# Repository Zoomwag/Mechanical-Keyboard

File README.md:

# Mechanical Keyboard

These are some high-quality renders of the keyboard design.

---

## Overview

This is a custom mechanical keyboard that I designed from scratch. It is a **60% layout** and runs on a **Raspberry Pi Pico** using **QMK firmware**.

The goal of this project was to make the keyboard:
- Easy to build  
- Affordable and accessible  
- Fully DIY-friendly  

All components are **through-hole (THT)**, making soldering much easier—especially for beginners. The entire keyboard is assembled using just **four M3 screws**, keeping the construction simple and clean.

The case is fully **3D printable**, and the keycaps can either be 3D printed or purchased. I recommend buying keycaps for better durability and finish.

The keyboard uses **Cherry MX-style switches**, so you can choose whichever type suits your preference. I will likely be using **Cherry MX Red switches** for a smooth, linear feel.

---

## PCB

### PCB Layout

### Schematic

### 3D PCB Model

### Fully Assembled PCB (3D View)

---

## Case

### Top Shell

### Bottom Shell

### Full Case (No Electronics)

### Electronics Installed

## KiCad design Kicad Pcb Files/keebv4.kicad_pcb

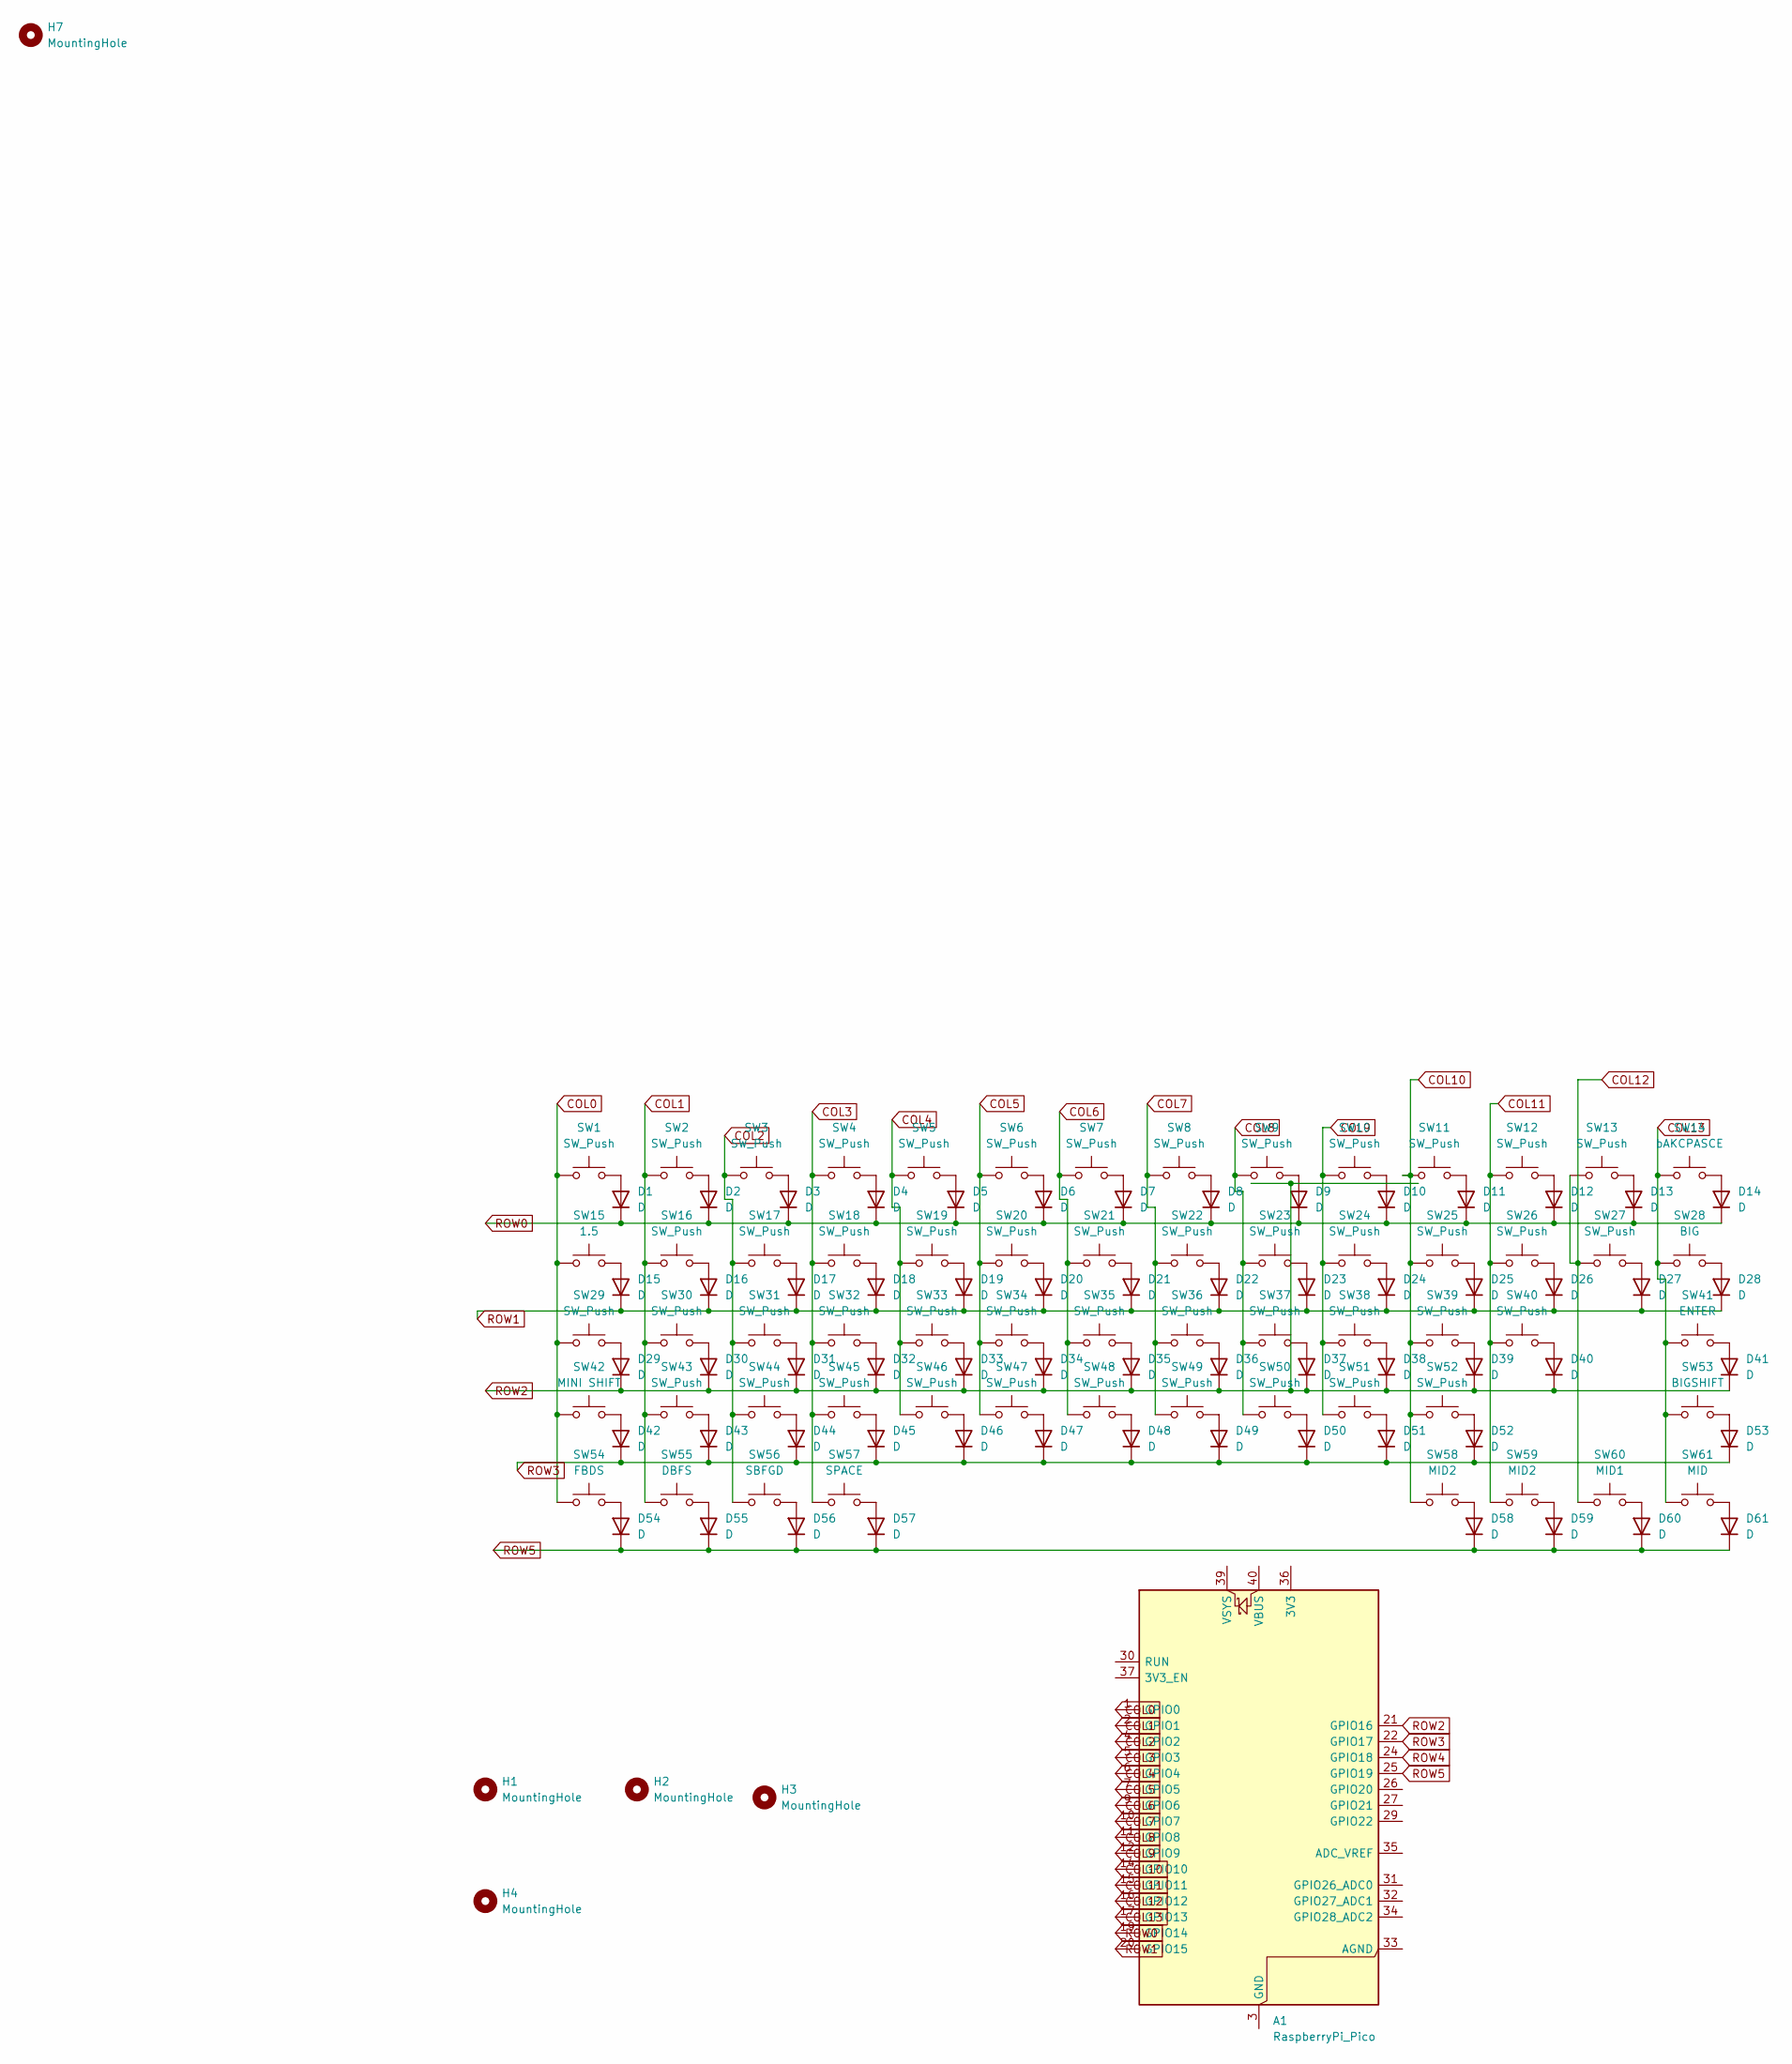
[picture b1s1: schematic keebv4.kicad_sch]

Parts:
A1: RaspberryPi_Pico; RaspberryPi_Pico_Common_Unspecified
D1, D2, D3, D4, D5, D6, D7, D8, D9, D10, D11, D12, D13, D14, D15, D16, D17, D18, D19, D20, D21, D22, D23, D24, D25, D26, D27, D28, D29, D30, D31, D32, D33, D34, D35, D36, D37, D38, D39, D40, D41, D42, D43, D44, D45, D46, D47, D48, D49, D50, D51, D52, D53, D54, D55, D56, D57, D58, D59, D60, D61: D; D_DO-35_SOD27_P7.62mm_Horizontal
H1, H2, H3, H4, H7: MountingHole; MountingHole_3.2mm_M3
SW1, SW2, SW3, SW4, SW5, SW6, SW7, SW8, SW9, SW10, SW11, SW12, SW13, SW16, SW17, SW18, SW19, SW20, SW21, SW22, SW23, SW24, SW25, SW26, SW27, SW30, SW31, SW32, SW33, SW34, SW35, SW36, SW37, SW38, SW39, SW40, SW43, SW44, SW45, SW46, SW47, SW48, SW49, SW50, SW51, SW52: SW_Push; SW_Cherry_MX_1.00u_PCB
SW14: bAKCPASCE; SW_Cherry_MX_2.00u_PCB
SW15: 1.5; SW_Cherry_MX_1.00u_PCB
SW28: BIG; SW_Cherry_MX_1.50u_PCB
SW29: SW_Push; SW_Cherry_MX_1.75u_PCB
SW41: ENTER; SW_Cherry_MX_2.25u_PCB
SW42: MINI SHIFT; SW_Cherry_MX_2.25u_PCB
SW53: BIGSHIFT; SW_Cherry_MX_2.75u_PCB
SW54: FBDS; SW_Cherry_MX_1.25u_PCB
SW55: DBFS; SW_Cherry_MX_1.25u_PCB
SW56: SBFGD; SW_Cherry_MX_1.25u_PCB
SW57: SPACE; SW_Cherry_MX_6.25u_PCB
SW58, SW59: MID2; SW_Cherry_MX_1.25u_PCB
SW60: MID1; SW_Cherry_MX_1.25u_PCB
SW61: MID; SW_Cherry_MX_1.25u_PCB

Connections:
COL0: A1.1 (GPIO0), SW1.1, SW15.1, SW29.1, SW42.1, SW54.1
COL1: A1.2 (GPIO1), SW2.1, SW16.1, SW30.1, SW43.1, SW55.1
COL2: A1.4 (GPIO2), SW3.1, SW17.1, SW31.1, SW44.1, SW56.1
COL3: A1.5 (GPIO3), SW4.1, SW18.1, SW32.1, SW45.1, SW57.1
COL4: A1.6 (GPIO4), SW5.1, SW19.1, SW33.1, SW46.1
COL5: A1.7 (GPIO5), SW6.1, SW20.1, SW34.1, SW47.1
COL6: A1.9 (GPIO6), SW7.1, SW21.1, SW35.1, SW48.1
COL7: A1.10 (GPIO7), SW8.1, SW22.1, SW36.1, SW49.1
COL8: A1.11 (GPIO8), SW9.1, SW23.1, SW37.1, SW50.1
COL9: A1.12 (GPIO9), SW10.1, SW24.1, SW38.1, SW51.1
COL10: A1.14 (GPIO10), SW11.1, SW25.1, SW39.1, SW52.1, SW58.1
COL11: A1.15 (GPIO11), SW12.1, SW26.1, SW40.1, SW59.1
COL12: A1.16 (GPIO12), SW13.1, SW27.1, SW60.1
COL13: A1.17 (GPIO13), SW14.1, SW28.1, SW41.1, SW53.1, SW61.1
unnamed: A1.3 (GND), A1.8 (GND), A1.13 (GND), A1.18 (GND), A1.23 (GND), A1.28 (GND), A1.38 (GND)
unnamed: D1.2 (A), SW1.2
unnamed: D2.2 (A), SW2.2
unnamed: D3.2 (A), SW3.2
unnamed: D4.2 (A), SW4.2
unnamed: D5.2 (A), SW5.2
unnamed: D6.2 (A), SW6.2
unnamed: D7.2 (A), SW7.2
unnamed: D8.2 (A), SW8.2
unnamed: D9.2 (A), SW9.2
unnamed: D10.2 (A), SW10.2
unnamed: D11.2 (A), SW11.2
unnamed: D12.2 (A), SW12.2
unnamed: D13.2 (A), SW13.2
unnamed: D14.2 (A), SW14.2
unnamed: D15.2 (A), SW15.2
unnamed: D16.2 (A), SW16.2
unnamed: D17.2 (A), SW17.2
unnamed: D18.2 (A), SW18.2
unnamed: D19.2 (A), SW19.2
unnamed: D20.2 (A), SW20.2
unnamed: D21.2 (A), SW21.2
unnamed: D22.2 (A), SW22.2
unnamed: D23.2 (A), SW23.2
unnamed: D24.2 (A), SW24.2
unnamed: D25.2 (A), SW25.2
unnamed: D26.2 (A), SW26.2
unnamed: D27.2 (A), SW27.2
unnamed: D28.2 (A), SW28.2
unnamed: D29.2 (A), SW29.2
unnamed: D30.2 (A), SW30.2
unnamed: D31.2 (A), SW31.2
unnamed: D32.2 (A), SW32.2
unnamed: D33.2 (A), SW33.2
unnamed: D34.2 (A), SW34.2
unnamed: D35.2 (A), SW35.2
unnamed: D36.2 (A), SW36.2
unnamed: D37.2 (A), SW37.2
unnamed: D38.2 (A), SW38.2
unnamed: D39.2 (A), SW39.2
unnamed: D40.2 (A), SW40.2
unnamed: D41.2 (A), SW41.2
unnamed: D42.2 (A), SW42.2
unnamed: D43.2 (A), SW43.2
unnamed: D44.2 (A), SW44.2
unnamed: D45.2 (A), SW45.2
unnamed: D46.2 (A), SW46.2
unnamed: D47.2 (A), SW47.2
unnamed: D48.2 (A), SW48.2
unnamed: D49.2 (A), SW49.2
unnamed: D50.2 (A), SW50.2
unnamed: D51.2 (A), SW51.2
unnamed: D52.2 (A), SW52.2
unnamed: D53.2 (A), SW53.2
unnamed: D54.2 (A), SW54.2
unnamed: D55.2 (A), SW55.2
unnamed: D56.2 (A), SW56.2
unnamed: D57.2 (A), SW57.2
unnamed: D58.2 (A), SW58.2
unnamed: D59.2 (A), SW59.2
unnamed: D60.2 (A), SW60.2
unnamed: D61.2 (A), SW61.2
ROW0: A1.19 (GPIO14), D1.1 (K), D2.1 (K), D3.1 (K), D4.1 (K), D5.1 (K), D6.1 (K), D7.1 (K), D8.1 (K), D9.1 (K), D10.1 (K), D11.1 (K), D12.1 (K), D13.1 (K), D14.1 (K)
ROW1: A1.20 (GPIO15), D15.1 (K), D16.1 (K), D17.1 (K), D18.1 (K), D19.1 (K), D20.1 (K), D21.1 (K), D22.1 (K), D23.1 (K), D24.1 (K), D25.1 (K), D26.1 (K), D27.1 (K), D28.1 (K)
ROW2: A1.21 (GPIO16), D29.1 (K), D30.1 (K), D31.1 (K), D32.1 (K), D33.1 (K), D34.1 (K), D35.1 (K), D36.1 (K), D37.1 (K), D38.1 (K), D39.1 (K), D40.1 (K), D41.1 (K)
ROW3: A1.22 (GPIO17), D42.1 (K), D43.1 (K), D44.1 (K), D45.1 (K), D46.1 (K), D47.1 (K), D48.1 (K), D49.1 (K), D50.1 (K), D51.1 (K), D52.1 (K), D53.1 (K)
ROW4: A1.24 (GPIO18)
ROW5: A1.25 (GPIO19), D54.1 (K), D55.1 (K), D56.1 (K), D57.1 (K), D58.1 (K), D59.1 (K), D60.1 (K), D61.1 (K)

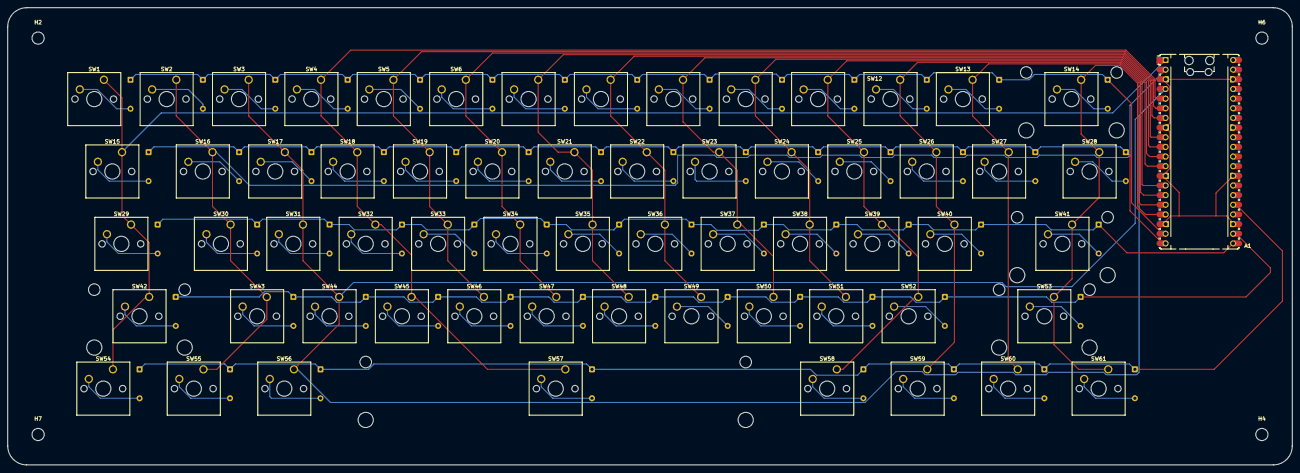
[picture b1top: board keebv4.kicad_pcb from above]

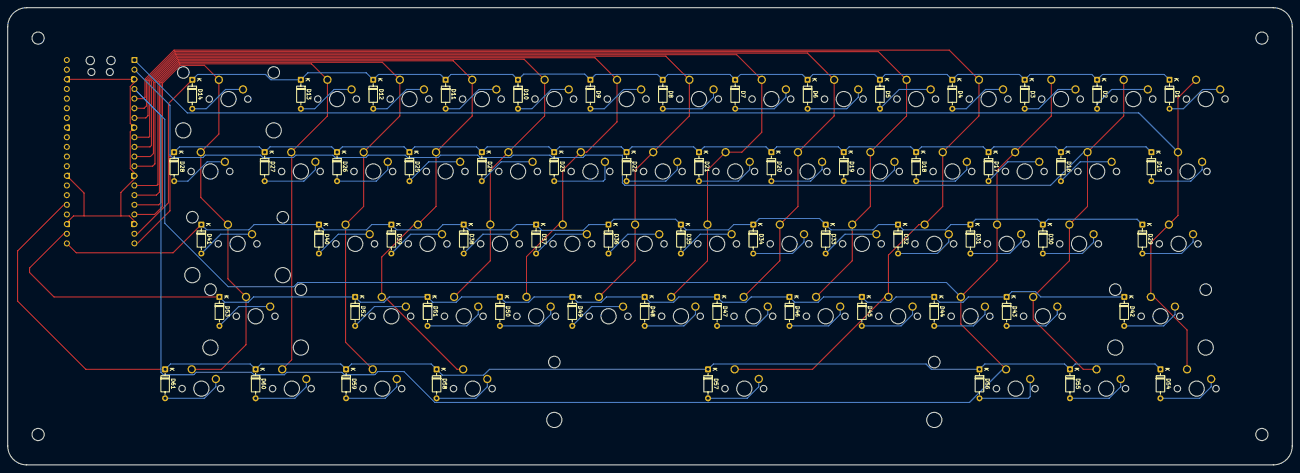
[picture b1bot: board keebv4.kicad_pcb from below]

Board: 2 copper layers, 338.1 x 120.3 mm, 127 parts (61 on the bottom side), 81 nets.

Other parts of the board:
H6: MountingHole; MountingHole_3.2mm_M3

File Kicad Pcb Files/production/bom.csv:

Designator,Footprint,Quantity,Value,LCSC Part #
A1,RaspberryPi_Pico_Common_Unspecified,1,RaspberryPi_Pico,
"D1, D10, D11, D12, D13, D14, D15, D16, D17, D18, D19, D2, D20, D21, D22, D23, D24, D25, D26, D27, D28, D29, D3, D30, D31, D32, D33, D34, D35, D36, D37, D38, D39, D4, D40, D41, D42, D43, D44, D45, D46, D47, D48, D49, D5, D50, D51, D52, D53, D54, D55, D56, D57, D58, D59, D6, D60, D61, D7, D8, D9",D_DO-35_SOD27_P7.62mm_Horizontal,61,D,
"SW1, SW10, SW11, SW12, SW13, SW16, SW17, SW18, SW19, SW2, SW20, SW21, SW22, SW23, SW24, SW25, SW26, SW27, SW3, SW30, SW31, SW32, SW33, SW34, SW35, SW36, SW37, SW38, SW39, SW4, SW40, SW43, SW44, SW45, SW46, SW47, SW48, SW49, SW5, SW50, SW51, SW52, SW6, SW7, SW8, SW9",SW_Cherry_MX_1.00u_PCB,46,SW_Push,
SW14,SW_Cherry_MX_2.00u_PCB,1,bAKCPASCE,
SW15,SW_Cherry_MX_1.00u_PCB,1,1.5,
SW28,SW_Cherry_MX_1.50u_PCB,1,BIG,
SW29,SW_Cherry_MX_1.75u_PCB,1,SW_Push,
SW41,SW_Cherry_MX_2.25u_PCB,1,ENTER,
SW42,SW_Cherry_MX_2.25u_PCB,1,MINI SHIFT,
SW53,SW_Cherry_MX_2.75u_PCB,1,BIGSHIFT,
SW54,SW_Cherry_MX_1.25u_PCB,1,FBDS,
SW55,SW_Cherry_MX_1.25u_PCB,1,DBFS,
SW56,SW_Cherry_MX_1.25u_PCB,1,SBFGD,
SW57,SW_Cherry_MX_6.25u_PCB,1,SPACE,
"SW58, SW59",SW_Cherry_MX_1.25u_PCB,2,MID2,
SW60,SW_Cherry_MX_1.25u_PCB,1,MID1,
SW61,SW_Cherry_MX_1.25u_PCB,1,MID,

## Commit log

2026-04-26 Rename keebv4.zip to GerberFiles.zip
2026-04-26 Rename My custom ISO keeb-bom.csv to BOM.csv
2026-04-26 Rename 0_sixty_base_default.hex to Firmware.hex
